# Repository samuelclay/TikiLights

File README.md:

# TikiLights
Hand-held tiki lights with color customization and a 3d printed Tiki mask

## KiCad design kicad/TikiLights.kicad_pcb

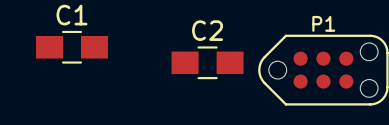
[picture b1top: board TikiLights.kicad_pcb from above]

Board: 2 copper layers, 3 parts (0 on the bottom side), 2 nets, no tracks yet.

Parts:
C1: 0.47µF; C_0805_HandSoldering
C2: C; C_0805_HandSoldering
P1: TC2030-CTX; TC2030-NL_SMALL

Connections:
+3V3: C1.1, C2.1
GND: C1.2, C2.2

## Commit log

2018-02-26 Initial commit, stubbing in STM32F030 32-pin and 6-pin SWD Tag Connect programming header.
2018-03-16 Got the tiki mask outline in eagle. Still need to build the level shifter and then connect all the nets.
2018-03-16 Datasheets, eagle, and kicad. Nothing works yet.
2018-03-16 Deleting locks.
2018-03-17 Schematic is finished. Screw holes added. Need board layout and updated CAD model for dimensions.
2018-03-17 Updating board to fit resized mask. Battery pack now fits and everything is in place for routing. Mask still needs a hook, and board needs a message.
2018-03-17 Adjusting lights positioning.
2018-03-19 Submitting tikilights v1. Both board and cad. Hope I didn't forget anything!
2018-04-15 Revision 2. Fixing TXB0102 board. Widening encoder side drill holes.
2018-04-17 Adding demo app.
2018-05-01 Adding firmware and cleaning up unused board files.
2018-05-02 Custom printed ear control for rotary encoders.
2018-05-02 Updating Cube, adding random color button. Fixing SPI.
2018-05-03 Intensity button toggle between bright and dim.
